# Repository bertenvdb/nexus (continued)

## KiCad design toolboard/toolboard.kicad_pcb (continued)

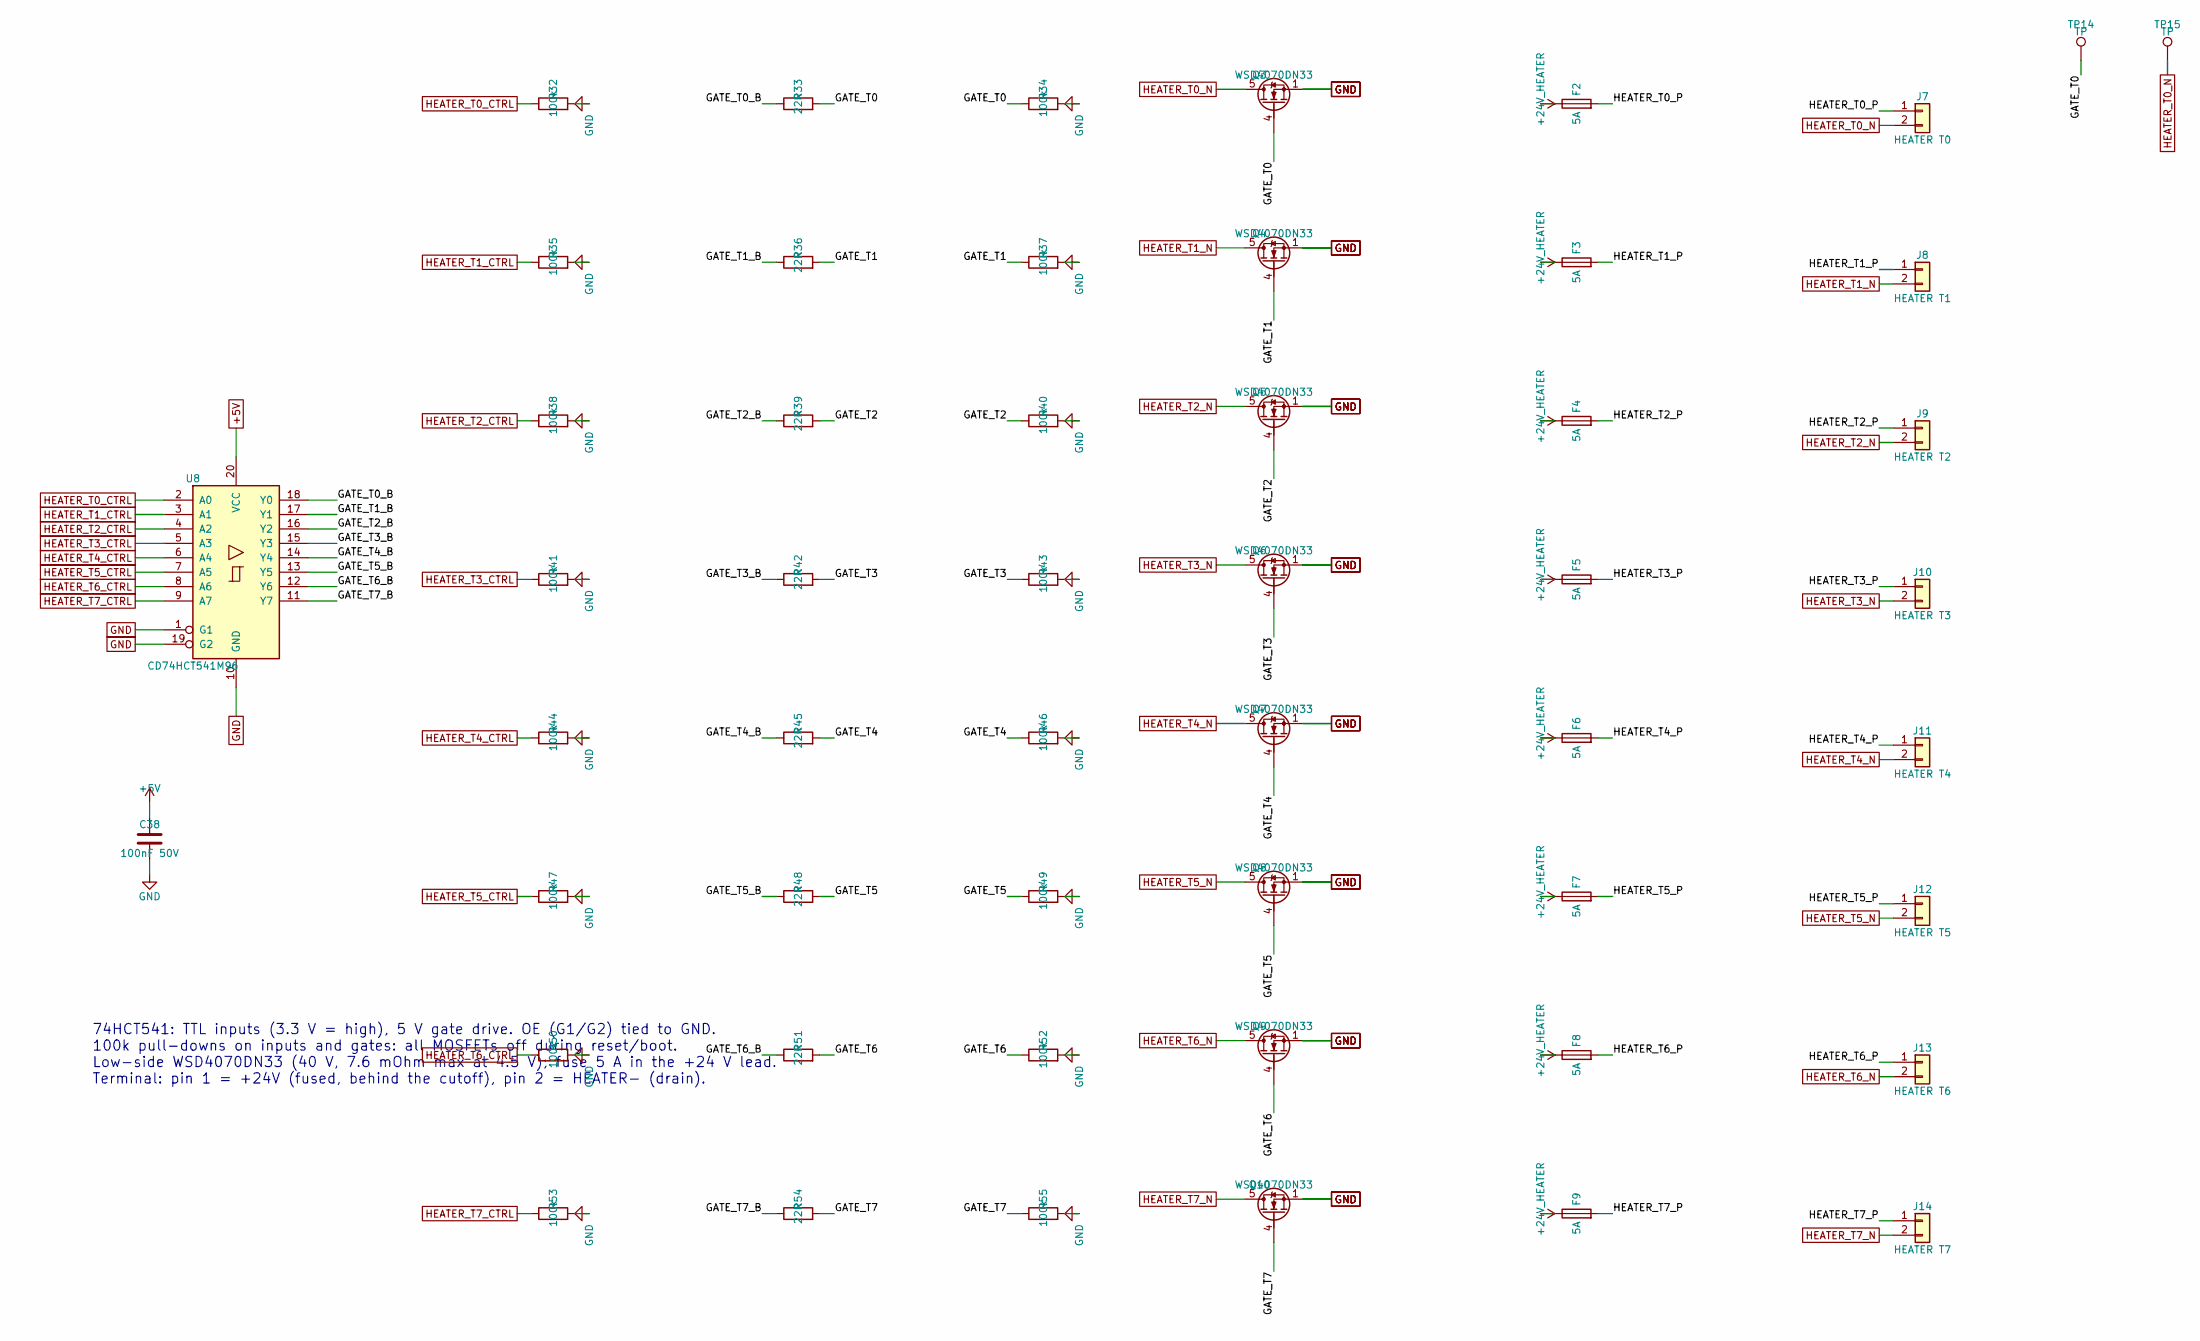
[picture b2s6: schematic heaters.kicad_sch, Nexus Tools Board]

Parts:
C38: 100nF 50V; C_0603_1608Metric; MPN CC0603KRX7R9BB104; LCSC C14663
F2, F3, F4, F5, F6, F7, F8, F9: 5A; Fuse_1206_3216Metric; MPN 0466005.NRHF; LCSC C57525
J7: HEATER T0; TerminalBlock_Phoenix_MKDS-1,5-2-5.08_1x02_P5.08mm_Horizont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; MPN WJ500V-5.08-2P; LCSC C8465
J8: HEATER T1; TerminalBlock_Phoenix_MKDS-1,5-2-5.08_1x02_P5.08mm_Horizont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; MPN WJ500V-5.08-2P; LCSC C8465
J9: HEATER T2; TerminalBlock_Phoenix_MKDS-1,5-2-5.08_1x02_P5.08mm_Horizont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; MPN WJ500V-5.08-2P; LCSC C8465
J10: HEATER T3; TerminalBlock_Phoenix_MKDS-1,5-2-5.08_1x02_P5.08mm_Horizont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; MPN WJ500V-5.08-2P; LCSC C8465
J11: HEATER T4; TerminalBlock_Phoenix_MKDS-1,5-2-5.08_1x02_P5.08mm_Horizont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; MPN WJ500V-5.08-2P; LCSC C8465
J12: HEATER T5; TerminalBlock_Phoenix_MKDS-1,5-2-5.08_1x02_P5.08mm_Horizont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; MPN WJ500V-5.08-2P; LCSC C8465
J13: HEATER T6; TerminalBlock_Phoenix_MKDS-1,5-2-5.08_1x02_P5.08mm_Horizont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; MPN WJ500V-5.08-2P; LCSC C8465
J14: HEATER T7; TerminalBlock_Phoenix_MKDS-1,5-2-5.08_1x02_P5.08mm_Horizont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; MPN WJ500V-5.08-2P; LCSC C8465
Q3, Q4, Q5, Q6, Q7, Q8, Q9, Q10: WSD4070DN33; PDFN3333-8_L3.1-W3.2-P0.65-LS3.4-BL; MPN WSD4070DN33; LCSC C719095
R32, R34, R35, R37, R38, R40, R41, R43, R44, R46, R47, R49, R50, R52, R53, R55: 100k; R_0603_1608Metric; MPN 0603WAF1003T5E; LCSC C25803
R33, R36, R39, R42, R45, R48, R51, R54: 22R; R_0603_1608Metric; MPN 0603WAF220JT5E; LCSC C23345
TP14, TP15: TP; TestPoint_Pad_D1.5mm
U8: CD74HCT541M96; SOIC-20W_7.5x12.8mm_P1.27mm; MPN CD74HCT541M96; LCSC C6560

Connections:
+5V: C38.1, U8.20 (VCC); also elsewhere on the board
+24V_HEATER: F2.1, F3.1, F4.1, F5.1, F6.1, F7.1, F8.1, F9.1; also elsewhere on the board
/heaters/GATE_T0: Q3.4 (G), R33.2, R34.1, TP14.1
/heaters/GATE_T0_B: R33.1, U8.18 (Y0)
/heaters/GATE_T1: Q4.4 (G), R36.2, R37.1
/heaters/GATE_T1_B: R36.1, U8.17 (Y1)
/heaters/GATE_T2: Q5.4 (G), R39.2, R40.1
/heaters/GATE_T2_B: R39.1, U8.16 (Y2)
/heaters/GATE_T3: Q6.4 (G), R42.2, R43.1
/heaters/GATE_T3_B: R42.1, U8.15 (Y3)
/heaters/GATE_T4: Q7.4 (G), R45.2, R46.1
/heaters/GATE_T4_B: R45.1, U8.14 (Y4)
/heaters/GATE_T5: Q8.4 (G), R48.2, R49.1
/heaters/GATE_T5_B: R48.1, U8.13 (Y5)
/heaters/GATE_T6: Q9.4 (G), R51.2, R52.1
/heaters/GATE_T6_B: R51.1, U8.12 (Y6)
/heaters/GATE_T7: Q10.4 (G), R54.2, R55.1
/heaters/GATE_T7_B: R54.1, U8.11 (Y7)
/heaters/HEATER_T0_P: F2.2, J7.1
/heaters/HEATER_T1_P: F3.2, J8.1
/heaters/HEATER_T2_P: F4.2, J9.1
/heaters/HEATER_T3_P: F5.2, J10.1
/heaters/HEATER_T4_P: F6.2, J11.1
/heaters/HEATER_T5_P: F7.2, J12.1
/heaters/HEATER_T6_P: F8.2, J13.1
/heaters/HEATER_T7_P: F9.2, J14.1
GND: C38.2, Q3.1 (S), Q3.2 (S), Q3.3 (S), Q4.1 (S), Q4.2 (S), Q4.3 (S), Q5.1 (S), Q5.2 (S), Q5.3 (S), Q6.1 (S), Q6.2 (S), Q6.3 (S), Q7.1 (S), Q7.2 (S), Q7.3 (S), Q8.1 (S), Q8.2 (S), Q8.3 (S), Q9.1 (S), Q9.2 (S), Q9.3 (S), Q10.1 (S), Q10.2 (S), Q10.3 (S), R32.2, R34.2, R35.2, R37.2, R38.2, R40.2, R41.2, R43.2, R44.2, R46.2, R47.2, R49.2, R50.2, R52.2, R53.2, R55.2, U8.1 (G1), U8.10 (GND), U8.19 (G2); also elsewhere on the board
HEATER_T0_CTRL: R32.1, U8.2 (A0); also elsewhere on the board
HEATER_T0_N: J7.2, Q3.5 (D), TP15.1; also elsewhere on the board
HEATER_T1_CTRL: R35.1, U8.3 (A1); also elsewhere on the board
HEATER_T1_N: J8.2, Q4.5 (D); also elsewhere on the board
HEATER_T2_CTRL: R38.1, U8.4 (A2); also elsewhere on the board
HEATER_T2_N: J9.2, Q5.5 (D); also elsewhere on the board
HEATER_T3_CTRL: R41.1, U8.5 (A3); also elsewhere on the board
HEATER_T3_N: J10.2, Q6.5 (D); also elsewhere on the board
HEATER_T4_CTRL: R44.1, U8.6 (A4); also elsewhere on the board
HEATER_T4_N: J11.2, Q7.5 (D); also elsewhere on the board
HEATER_T5_CTRL: R47.1, U8.7 (A5); also elsewhere on the board
HEATER_T5_N: J12.2, Q8.5 (D); also elsewhere on the board
HEATER_T6_CTRL: R50.1, U8.8 (A6); also elsewhere on the board
HEATER_T6_N: J13.2, Q9.5 (D); also elsewhere on the board
HEATER_T7_CTRL: R53.1, U8.9 (A7); also elsewhere on the board
HEATER_T7_N: J14.2, Q10.5 (D); also elsewhere on the board

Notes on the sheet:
74HCT541: TTL inputs (3.3 V = high), 5 V gate drive. OE (G1/G2) tied to GND. 100k pull-downs on inputs and gates: all MOSFETs off during reset/boot. Low-side WSD4070DN33 (40 V, 7.6 mOhm max at 4.5 V); fuse 5 A in the +24 V lead. Terminal: pin 1 = +24V (fused, behind the cutoff), pin 2 = HEATER- (dr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

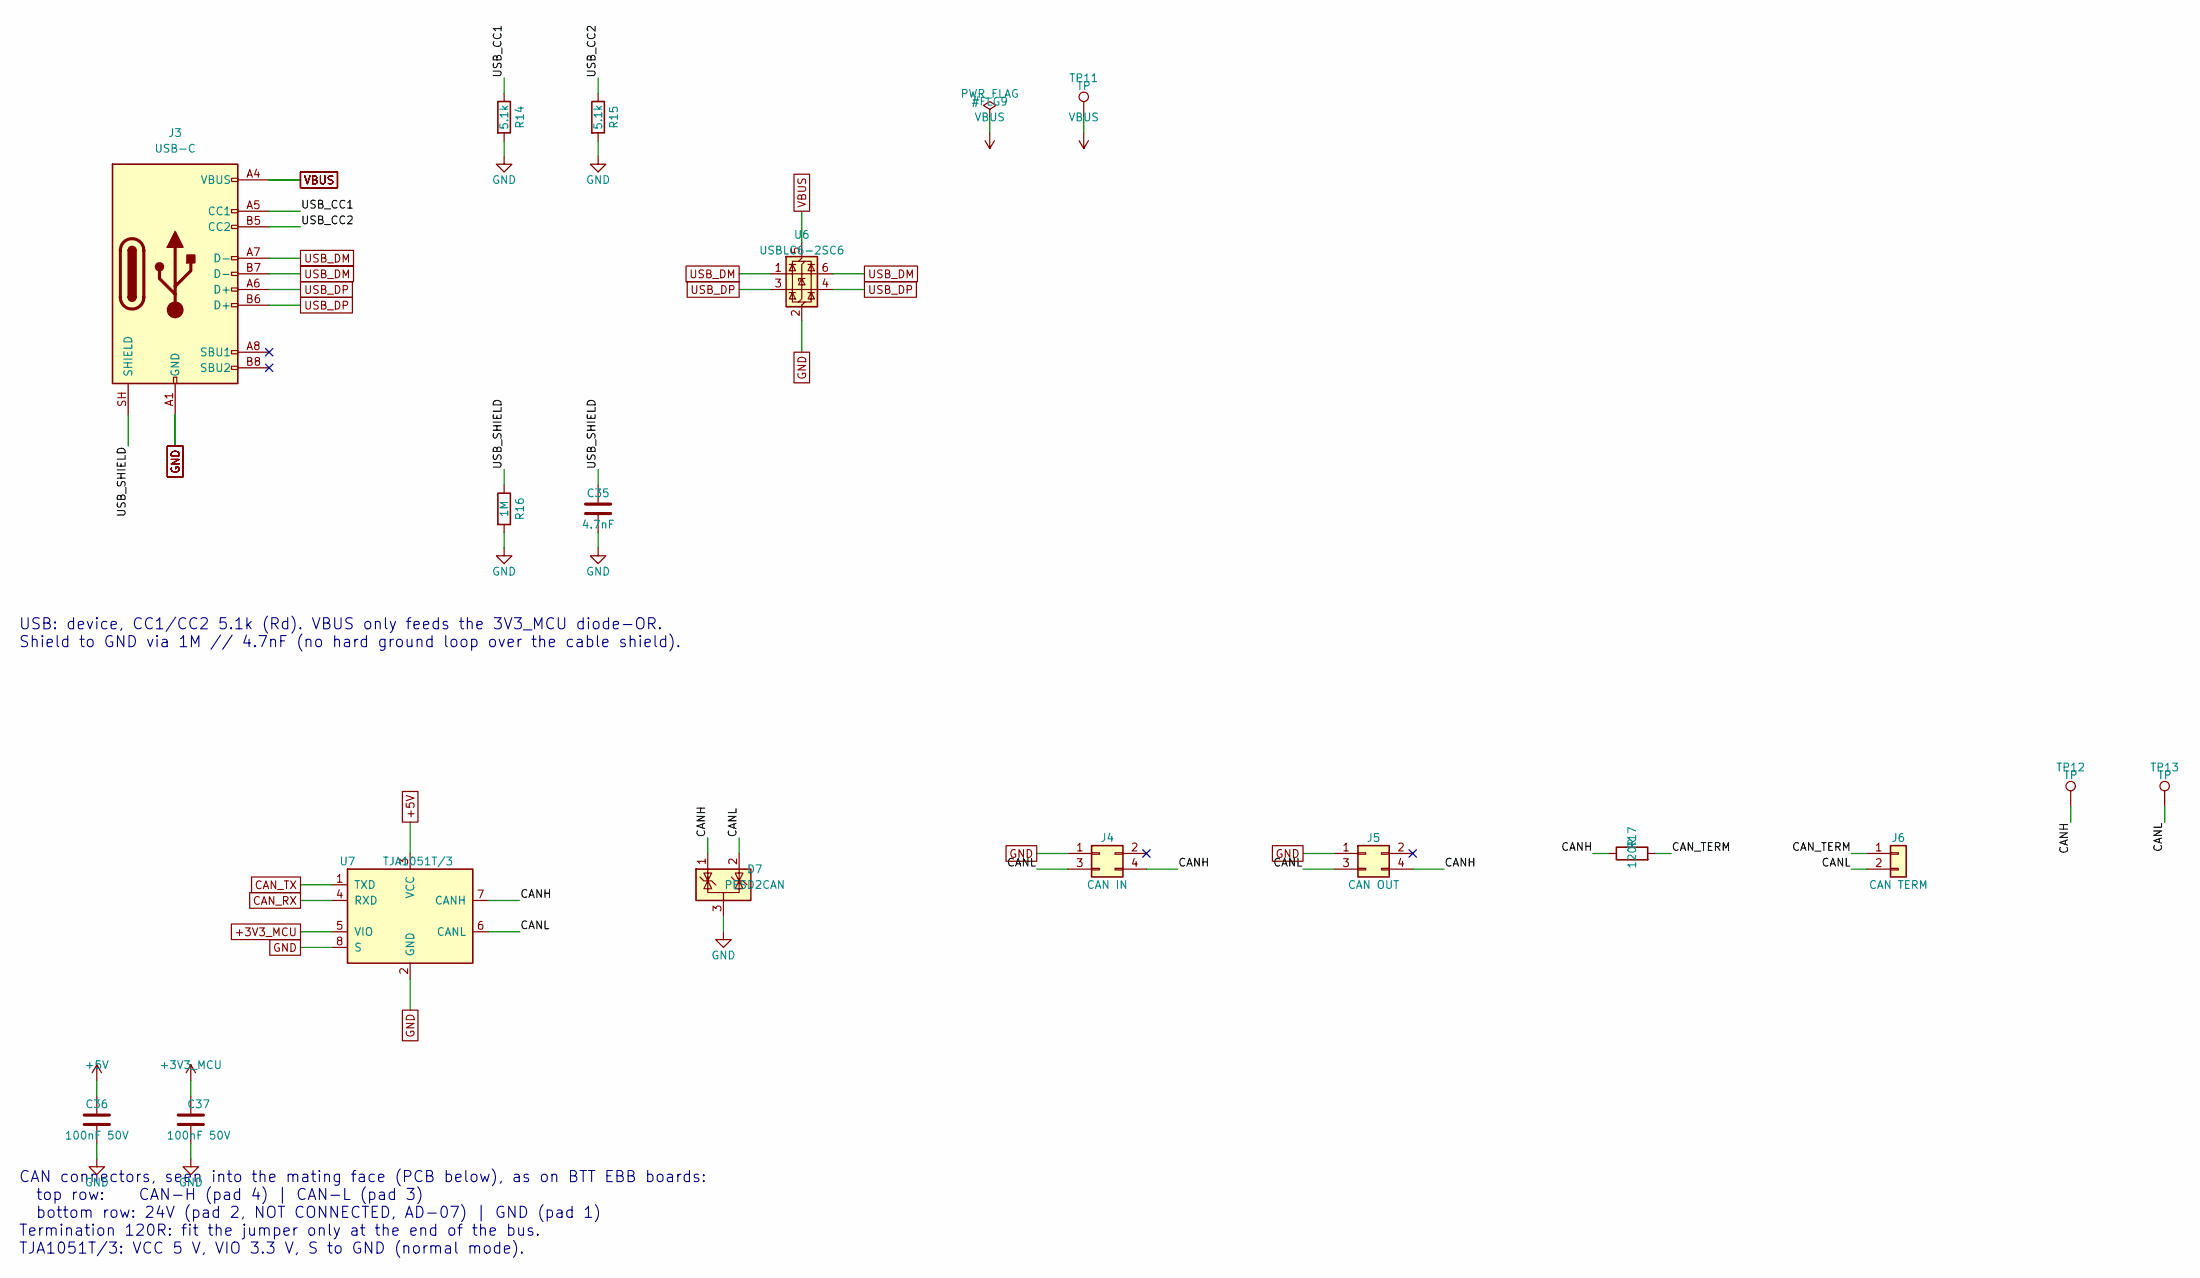
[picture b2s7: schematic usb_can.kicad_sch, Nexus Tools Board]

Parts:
C35: 4.7nF; C_0603_1608Metric; MPN 0603B472K500NT; LCSC C53987
C36, C37: 100nF 50V; C_0603_1608Metric; MPN CC0603KRX7R9BB104; LCSC C14663
D7: PESD2CAN; SOT-23; MPN PESD2CAN; LCSC C907830
J3: USB-C; USB_C_Receptacle_HRO_TYPE-C-31-M-12; MPN TYPE-C-31-M-12; LCSC C165948
J4: CAN IN; Molex_Micro-Fit_3.0_43045-0400_2x02_P3.00mm_Horizontal; MPN 43045-0400; LCSC C122413
J5: CAN OUT; Molex_Micro-Fit_3.0_43045-0400_2x02_P3.00mm_Horizontal; MPN 43045-0400; LCSC C122413
J6: CAN TERM; PinHeader_1x02_P2.54mm_Vertical; MPN PZ254V-11-02P; LCSC C492401
R14, R15: 5.1k; R_0603_1608Metric; MPN 0603WAF5101T5E; LCSC C23186
R16: 1M; R_0603_1608Metric; MPN 0603WAF1004T5E; LCSC C22935
R17: 120R; R_0603_1608Metric; MPN 0603WAF1200T5E; LCSC C22787
TP11, TP12, TP13: TP; TestPoint_Pad_D1.5mm
U6: USBLC6-2SC6; SOT-23-6; MPN USBLC6-2SC6; LCSC C7519
U7: TJA1051T/3; SOIC-8_3.9x4.9mm_P1.27mm; MPN TJA1051T/3/1J; LCSC C38695

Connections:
+3V3_MCU: C37.1, U7.5 (VIO); also elsewhere on the board
+5V: C36.1, U7.3 (VCC); also elsewhere on the board
/usb_can/CANH: D7.1 (K), J4.4, J5.4, R17.1, TP12.1, U7.7 (CANH)
/usb_can/CANL: D7.2 (K), J4.3, J5.3, J6.2, TP13.1, U7.6 (CANL)
/usb_can/CAN_TERM: J6.1, R17.2
/usb_can/USB_CC1: J3.A5 (CC1), R14.1
/usb_can/USB_CC2: J3.B5 (CC2), R15.1
/usb_can/USB_SHIELD: C35.1, J3.SH (SHIELD), R16.1
CAN_RX: U7.4 (RXD); also elsewhere on the board
CAN_TX: U7.1 (TXD); also elsewhere on the board
GND: C35.2, C36.2, C37.2, D7.3 (A), J3.A1 (GND), J3.A12 (GND), J3.B1 (GND), J3.B12 (GND), J4.1, J5.1, R14.2, R15.2, R16.2, U6.2 (GND), U7.2 (GND), U7.8 (S); also elsewhere on the board
USB_DM: J3.A7 (D-), J3.B7 (D-), U6.1 (I/O1), U6.6 (I/O1); also elsewhere on the board
USB_DP: J3.A6 (D+), J3.B6 (D+), U6.3 (I/O2), U6.4 (I/O2); also elsewhere on the board
VBUS: J3.A4 (VBUS), J3.A9 (VBUS), J3.B4 (VBUS), J3.B9 (VBUS), TP11.1, U6.5 (VBUS); also elsewhere on the board

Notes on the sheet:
CAN connectors, seen into the mating face (PCB below), as on BTT EBB boards: top row: CAN-H (pad 4) | CAN-L (pad 3) bottom row: 24V (pad 2, NOT CONNECTED, AD-07) | GND (pad 1) Termination 120R: fit the jumper only at the end of the bus. TJA1051T/3: VCC 5 V, VIO 3.3 V, S to GND (normal mode).
USB: device, CC1/CC2 5.1k (Rd). VBUS only feeds the 3V3_MCU diode-OR. Shield to GND via 1M // 4.7nF (no hard ground loop over the cable shield).

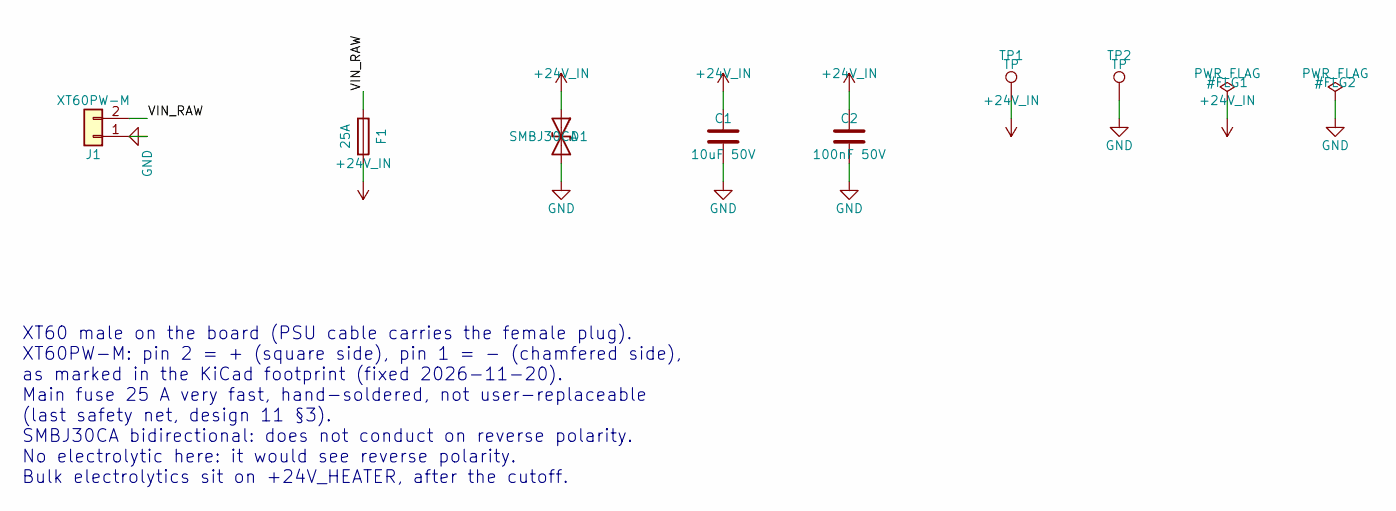
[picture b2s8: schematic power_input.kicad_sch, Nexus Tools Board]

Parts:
C1: 10uF 50V; C_1206_3216Metric; MPN CL31A106KBHNNNE; LCSC C13585
C2: 100nF 50V; C_0603_1608Metric; MPN CC0603KRX7R9BB104; LCSC C14663
D1: SMBJ30CA; D_SMB; MPN SMBJ30CA; LCSC C2925441
F1: 25A; FUSE-SMD_L10.1-W3.1; MPN 0456025.ER; LCSC C315877
J1: XT60PW-M; AMASS_XT60PW-M_1x02_P7.20mm_Horizontal; MPN XT60PW-M; LCSC C98732
TP1, TP2: TP; TestPoint_Pad_D1.5mm

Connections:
+24V_IN: C1.1, C2.1, D1.1 (A1), F1.2, TP1.1; also elsewhere on the board
/power_input/VIN_RAW: F1.1, J1.2
GND: C1.2, C2.2, D1.2 (A2), J1.1, TP2.1; also elsewhere on the board

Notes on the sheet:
XT60 male on the board (PSU cable carries the female plug). XT60PW-M: pin 2 = + (square side), pin 1 = - (chamfered side), as marked in the KiCad footprint (fixed 2026-11-20). Main fuse 25 A very fast, hand-soldered, not user-replaceable (last safety net, design 11 §3). SMBJ30CA bidirectional: does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

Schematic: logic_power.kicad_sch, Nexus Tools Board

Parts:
C12, C13: 10uF 50V; C_1206_3216Metric; MPN CL31A106KBHNNNE; LCSC C13585
C14, C17, C23, C27: 100nF 50V; C_0603_1608Metric; MPN CC0603KRX7R9BB104; LCSC C14663
C15: 22nF; C_0603_1608Metric; MPN CL10B223KB8NNNC; LCSC C21122
C16: 100pF C0G; C_0603_1608Metric; MPN CL10C101JB8NNNC; LCSC C14858
C18, C19, C20: 22uF 25V; C_1206_3216Metric; MPN CL31A226KAHNNNE; LCSC C12891
C21, C22, C24, C25, C26: 1uF 50V; C_0603_1608Metric; MPN CL10A105KB8NNNC; LCSC C15849
D3, D4: SS56C; D_SMC; MPN SS56C; LCSC C24138
D5, D6: B5819W; D_SOD-123; MPN B5819W SL; LCSC C8598
L1: 10uH; IND-SMD_L7.1-W6.6; MPN MWSA0603S-100MT; LCSC C132141
R6: 1M; R_0603_1608Metric; MPN 0603WAF1004T5E; LCSC C22935
R7: 68k; R_0603_1608Metric; MPN 0603WAF6802T5E; LCSC C23231
R8: 160k; R_0603_1608Metric; MPN 0603WAF1603T5E; LCSC C22813
R9, R11: 6.8k; R_0603_1608Metric; MPN 0603WAF6801T5E; LCSC C23212
R10: 36k; R_0603_1608Metric; MPN 0603WAF3602T5E; LCSC C23147
R12: 10R; R_0603_1608Metric; MPN 0603WAF100JT5E; LCSC C22859
TP6, TP7, TP8, TP9, TP10: TP; TestPoint_Pad_D1.5mm
U2: TPS54360B; TI_SO-PowerPAD-8_ThermalVias; MPN TPS54360BDDAR; LCSC C524806
U3, U4: ME6211C33; SOT-23-5; MPN ME6211C33M5G-N; LCSC C82942

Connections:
+3V3_AUX: C25.1, TP8.1, U4.5 (V_{OUT}); also elsewhere on the board
+3V3_MCU: C22.1, C23.1, R12.1, TP7.1, U3.5 (V_{OUT}); also elsewhere on the board
+5V: C18.1, C19.1, C20.1, C24.1, D5.2 (A), L1.2, R10.1, TP6.1, U4.1 (V_{IN}), U4.3 (CE); also elsewhere on the board
+24V_IN: D3.2 (A); also elsewhere on the board
/logic_power/+5V_OR: C21.1, D5.1 (K), D6.1 (K), U3.1 (V_{IN}), U3.3 (CE)
/logic_power/BUCK_BOOT: C17.1, U2.1 (BOOT)
/logic_power/BUCK_COMP: C16.1, R9.1, U2.6 (COMP)
/logic_power/BUCK_EN: R6.2, R7.1, U2.3 (EN)
/logic_power/BUCK_FB: R10.2, R11.1, U2.5 (FB)
/logic_power/BUCK_RT: R8.1, U2.4 (RT/CLK)
/logic_power/BUCK_SW: C17.2, D4.1 (K), L1.1, U2.8 (SW)
/logic_power/COMP_RC: C15.1, R9.2
/logic_power/VIN_BUCK: C12.1, C13.1, C14.1, D3.1 (K), R6.1, U2.2 (VIN)
AGND: C26.2, C27.2, TP10.1; also elsewhere on the board
GND: C12.2, C13.2, C14.2, C15.2, C16.2, C18.2, C19.2, C20.2, C21.2, C22.2, C23.2, C24.2, C25.2, D4.2 (A), R7.2, R8.2, R11.2, U2.7 (GND), U2.9 (GNDPAD), U3.2 (V_{SS}), U4.2 (V_{SS}); also elsewhere on the board
VBUS: D6.2 (A); also elsewhere on the board
VREF_A: C26.1, C27.1, R12.2, TP9.1; also elsewhere on the board

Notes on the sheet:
3V3_MCU: diode-OR of +5V and USB VBUS, so the MCU runs on USB alone (flashing without 24 V). VBUS feeds nothing else. 3V3_AUX: sensors, status LEDs. VREF_A = 3V3_MCU through 10R + 1uF + 100nF to AGND (ratiometric ADC).
TPS54360B, 604 kHz (RT 160k), Vout = 0.8 x (1 + 36k/6.8k) = 5.04 V. UVLO 1M/68k: start 17.6 V, stop 14.3 V. Compensation 6.8k + 22nF // 100pF. Catch diode SS56C: non-synchronous buck. Values: docs/calculations.md §1.

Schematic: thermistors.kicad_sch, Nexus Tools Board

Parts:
C39, C40, C41, C42, C43, C44, C45, C46, C47, C48, C49, C50, C51, C52, C53, C54: 100nF 50V; C_0603_1608Metric; MPN CC0603KRX7R9BB104; LCSC C14663
D22, D24, D26, D28, D30, D32, D34, D36: SMF30CA; D_SOD-123F; MPN SMF30CA; LCSC C19077519
D23, D25, D27, D29, D31, D33, D35, D37: BAT54S; SOT-23; MPN BAT54S; LCSC C408389
J15: THERM T0; JST_XH_B2B-XH-A_1x02_P2.50mm_Vertical; MPN B2B-XH-A(LF)(SN); LCSC C158012
J16: THERM T1; JST_XH_B2B-XH-A_1x02_P2.50mm_Vertical; MPN B2B-XH-A(LF)(SN); LCSC C158012
J17: THERM T2; JST_XH_B2B-XH-A_1x02_P2.50mm_Vertical; MPN B2B-XH-A(LF)(SN); LCSC C158012
J18: THERM T3; JST_XH_B2B-XH-A_1x02_P2.50mm_Vertical; MPN B2B-XH-A(LF)(SN); LCSC C158012
J19: THERM T4; JST_XH_B2B-XH-A_1x02_P2.50mm_Vertical; MPN B2B-XH-A(LF)(SN); LCSC C158012
J20: THERM T5; JST_XH_B2B-XH-A_1x02_P2.50mm_Vertical; MPN B2B-XH-A(LF)(SN); LCSC C158012
J21: THERM T6; JST_XH_B2B-XH-A_1x02_P2.50mm_Vertical; MPN B2B-XH-A(LF)(SN); LCSC C158012
J22: THERM T7; JST_XH_B2B-XH-A_1x02_P2.50mm_Vertical; MPN B2B-XH-A(LF)(SN); LCSC C158012
JP1, JP2, JP3, JP4, JP5, JP6, JP7, JP8: PT1000; SolderJumper-2_P1.3mm_Open_RoundedPad1.0x1.5mm
R56, R59, R62, R65, R68, R71, R74, R77: 4.7k 0.1%; R_0603_1608Metric; MPN TD03G4701BT; LCSC C666997
R57, R60, R63, R66, R69, R72, R75, R78: 4.12k 0.1%; R_0603_1608Metric; MPN AR03BTCX4121; LCSC C2984354
R58, R61, R64, R67, R70, R73, R76, R79: 4.7k; R_0603_1608Metric; MPN 0603WAF4701T5E; LCSC C23162

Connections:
/thermistors/THERM_T0_C: C39.1, D22.1 (A1), J15.1, R56.2, R57.2, R58.1
/thermistors/THERM_T0_PT: JP1.2 (B), R57.1
/thermistors/THERM_T1_C: C41.1, D24.1 (A1), J16.1, R59.2, R60.2, R61.1
/thermistors/THERM_T1_PT: JP2.2 (B), R60.1
/thermistors/THERM_T2_C: C43.1, D26.1 (A1), J17.1, R62.2, R63.2, R64.1
/thermistors/THERM_T2_PT: JP3.2 (B), R63.1
/thermistors/THERM_T3_C: C45.1, D28.1 (A1), J18.1, R65.2, R66.2, R67.1
/thermistors/THERM_T3_PT: JP4.2 (B), R66.1
/thermistors/THERM_T4_C: C47.1, D30.1 (A1), J19.1, R68.2, R69.2, R70.1
/thermistors/THERM_T4_PT: JP5.2 (B), R69.1
/thermistors/THERM_T5_C: C49.1, D32.1 (A1), J20.1, R71.2, R72.2, R73.1
/thermistors/THERM_T5_PT: JP6.2 (B), R72.1
/thermistors/THERM_T6_C: C51.1, D34.1 (A1), J21.1, R74.2, R75.2, R76.1
/thermistors/THERM_T6_PT: JP7.2 (B), R75.1
/thermistors/THERM_T7_C: C53.1, D36.1 (A1), J22.1, R77.2, R78.2, R79.1
/thermistors/THERM_T7_PT: JP8.2 (B), R78.1
AGND: C39.2, C40.2, C41.2, C42.2, C43.2, C44.2, C45.2, C46.2, C47.2, C48.2, C49.2, C50.2, C51.2, C52.2, C53.2, C54.2, D22.2 (A2), D23.1 (A), D24.2 (A2), D25.1 (A), D26.2 (A2), D27.1 (A), D28.2 (A2), D29.1 (A), D30.2 (A2), D31.1 (A), D32.2 (A2), D33.1 (A), D34.2 (A2), D35.1 (A), D36.2 (A2), D37.1 (A), J15.2, J16.2, J17.2, J18.2, J19.2, J20.2, J21.2, J22.2; also elsewhere on the board
THERM_T0: C40.1, D23.3 (COM), R58.2; also elsewhere on the board
THERM_T1: C42.1, D25.3 (COM), R61.2; also elsewhere on the board
THERM_T2: C44.1, D27.3 (COM), R64.2; also elsewhere on the board
THERM_T3: C46.1, D29.3 (COM), R67.2; also elsewhere on the board
THERM_T4: C48.1, D31.3 (COM), R70.2; also elsewhere on the board
THERM_T5: C50.1, D33.3 (COM), R73.2; also elsewhere on the board
THERM_T6: C52.1, D35.3 (COM), R76.2; also elsewhere on the board
THERM_T7: C54.1, D37.3 (COM), R79.2; also elsewhere on the board
VREF_A: D23.2 (K), D25.2 (K), D27.2 (K), D29.2 (K), D31.2 (K), D33.2 (K), D35.2 (K), D37.2 (K), JP1.1 (A), JP2.1 (A), JP3.1 (A), JP4.1 (A), JP5.1 (A), JP6.1 (A), JP7.1 (A), JP8.1 (A), R56.1, R59.1, R62.1, R65.1, R68.1, R71.1, R74.1, R77.1; also elsewhere on the board

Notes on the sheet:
Pull-up 4.7k 0.1 % (NTC 100K, pullup_resistor: 4700). Close JP = PT1000: 4.7k // 4.12k = 2195 Ohm (pullup_resistor: 2195). Pull-ups on VREF_A = ADC reference. 24 V on the input (heater wire touching the thermistor wire): 4.7k + BAT54S limit the ADC pin current to ~4 mA; SMF30CA does not conduct at 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

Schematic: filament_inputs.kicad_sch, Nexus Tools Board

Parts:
C55: 10uF 50V; C_1206_3216Metric; MPN CL31A106KBHNNNE; LCSC C13585
C56, C57, C58, C59, C60, C61, C62, C63, C64, C65, C66, C67, C68, C69, C70, C71: 100nF 50V; C_0603_1608Metric; MPN CC0603KRX7R9BB104; LCSC C14663
D38, D39, D40, D41, D42, D43, D44, D45, D46, D47, D48, D49, D50, D51, D52, D53, D54: PESD5V0S1BA; D_SOD-323; MPN PESD5V0S1BA; LCSC C2827694
F10: 0.75A; Fuse_1206_3216Metric; MPN JK-nSMD075-16; LCSC C409806
J23: FIL T0; JST_XH_B4B-XH-A_1x04_P2.50mm_Vertical; MPN B4B-XH-A(LF)(SN); LCSC C144395
J24: FIL T1; JST_XH_B4B-XH-A_1x04_P2.50mm_Vertical; MPN B4B-XH-A(LF)(SN); LCSC C144395
J25: FIL T2; JST_XH_B4B-XH-A_1x04_P2.50mm_Vertical; MPN B4B-XH-A(LF)(SN); LCSC C144395
J26: FIL T3; JST_XH_B4B-XH-A_1x04_P2.50mm_Vertical; MPN B4B-XH-A(LF)(SN); LCSC C144395
J27: FIL T4; JST_XH_B4B-XH-A_1x04_P2.50mm_Vertical; MPN B4B-XH-A(LF)(SN); LCSC C144395
J28: FIL T5; JST_XH_B4B-XH-A_1x04_P2.50mm_Vertical; MPN B4B-XH-A(LF)(SN); LCSC C144395
J29: FIL T6; JST_XH_B4B-XH-A_1x04_P2.50mm_Vertical; MPN B4B-XH-A(LF)(SN); LCSC C144395
J30: FIL T7; JST_XH_B4B-XH-A_1x04_P2.50mm_Vertical; MPN B4B-XH-A(LF)(SN); LCSC C144395
JP9: VCC_FIL 5V|3V3; SolderJumper-3_P1.3mm_Bridged12_RoundedPad1.0x1.5mm
R80, R82, R84, R86, R88, R90, R92, R94, R96, R98, R100, R102, R104, R106, R108, R110: 1k; R_0603_1608Metric; MPN 0603WAF1001T5E; LCSC C21190
R81, R83, R85, R87, R89, R91, R93, R95, R97, R99, R101, R103, R105, R107, R109, R111: 10k; R_0603_1608Metric; MPN 0603WAF1002T5E; LCSC C25804

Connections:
+3V3_AUX: JP9.3 (B); also elsewhere on the board
+3V3_MCU: R81.1, R83.1, R85.1, R87.1, R89.1, R91.1, R93.1, R95.1, R97.1, R99.1, R101.1, R103.1, R105.1, R107.1, R109.1, R111.1; also elsewhere on the board
+5V: JP9.1 (A); also elsewhere on the board
/filament_inputs/FIL_MOTION_T0_C: D40.1 (A1), J23.4, R82.1
/filament_inputs/FIL_MOTION_T1_C: D42.1 (A1), J24.4, R86.1
/filament_inputs/FIL_MOTION_T2_C: D44.1 (A1), J25.4, R90.1
/filament_inputs/FIL_MOTION_T3_C: D46.1 (A1), J26.4, R94.1
/filament_inputs/FIL_MOTION_T4_C: D48.1 (A1), J27.4, R98.1
/filament_inputs/FIL_MOTION_T5_C: D50.1 (A1), J28.4, R102.1
/filament_inputs/FIL_MOTION_T6_C: D52.1 (A1), J29.4, R106.1
/filament_inputs/FIL_MOTION_T7_C: D54.1 (A1), J30.4, R110.1
/filament_inputs/FIL_RUNOUT_T0_C: D39.1 (A1), J23.1, R80.1
/filament_inputs/FIL_RUNOUT_T1_C: D41.1 (A1), J24.1, R84.1
/filament_inputs/FIL_RUNOUT_T2_C: D43.1 (A1), J25.1, R88.1
/filament_inputs/FIL_RUNOUT_T3_C: D45.1 (A1), J26.1, R92.1
/filament_inputs/FIL_RUNOUT_T4_C: D47.1 (A1), J27.1, R96.1
/filament_inputs/FIL_RUNOUT_T5_C: D49.1 (A1), J28.1, R100.1
/filament_inputs/FIL_RUNOUT_T6_C: D51.1 (A1), J29.1, R104.1
/filament_inputs/FIL_RUNOUT_T7_C: D53.1 (A1), J30.1, R108.1
/filament_inputs/VCC_FIL: C55.1, D38.1 (A1), F10.2, J23.3, J24.3, J25.3, J26.3, J27.3, J28.3, J29.3, J30.3
/filament_inputs/VCC_FIL_SEL: F10.1, JP9.2 (C)
FIL_MOTION_T0: C57.1, R82.2, R83.2; also elsewhere on the board
FIL_MOTION_T1: C59.1, R86.2, R87.2; also elsewhere on the board
FIL_MOTION_T2: C61.1, R90.2, R91.2; also elsewhere on the board
FIL_MOTION_T3: C63.1, R94.2, R95.2; also elsewhere on the board
FIL_MOTION_T4: C65.1, R98.2, R99.2; also elsewhere on the board
FIL_MOTION_T5: C67.1, R102.2, R103.2; also elsewhere on the board
FIL_MOTION_T6: C69.1, R106.2, R107.2; also elsewhere on the board
FIL_MOTION_T7: C71.1, R110.2, R111.2; also elsewhere on the board
FIL_RUNOUT_T0: C56.1, R80.2, R81.2; also elsewhere on the board
FIL_RUNOUT_T1: C58.1, R84.2, R85.2; also elsewhere on the board
FIL_RUNOUT_T2: C60.1, R88.2, R89.2; also elsewhere on the board
FIL_RUNOUT_T3: C62.1, R92.2, R93.2; also elsewhere on the board
FIL_RUNOUT_T4: C64.1, R96.2, R97.2; also elsewhere on the board
FIL_RUNOUT_T5: C66.1, R100.2, R101.2; also elsewhere on the board
FIL_RUNOUT_T6: C68.1, R104.2, R105.2; also elsewhere on the board
FIL_RUNOUT_T7: C70.1, R108.2, R109.2; also elsewhere on the board
GND: C55.2, C56.2, C57.2, C58.2, C59.2, C60.2, C61.2, C62.2, C63.2, C64.2, C65.2, C66.2, C67.2, C68.2, C69.2, C70.2, C71.2, D38.2 (A2), D39.2 (A2), D40.2 (A2), D41.2 (A2), D42.2 (A2), D43.2 (A2), D44.2 (A2), D45.2 (A2), D46.2 (A2), D47.2 (A2), D48.2 (A2), D49.2 (A2), D50.2 (A2), D51.2 (A2), D52.2 (A2), D53.2 (A2), D54.2 (A2), J23.2, J24.2, J25.2, J26.2, J27.2, J28.2, J29.2, J30.2; also elsewhere on the board

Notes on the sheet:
Port: 1 RUNOUT, 2 GND, 3 VCC, 4 MOTION (silkscreen). D2F: pins 1 + 2. Inputs: 1k + 100nF (tau 0.1 ms), 10k pull-up to 3V3 (unplugged = high), FT pins (5V tolerant). VCC_FIL default 5 V (jumper 1-2); 3.3 V via 2-3: max 100 mA total.

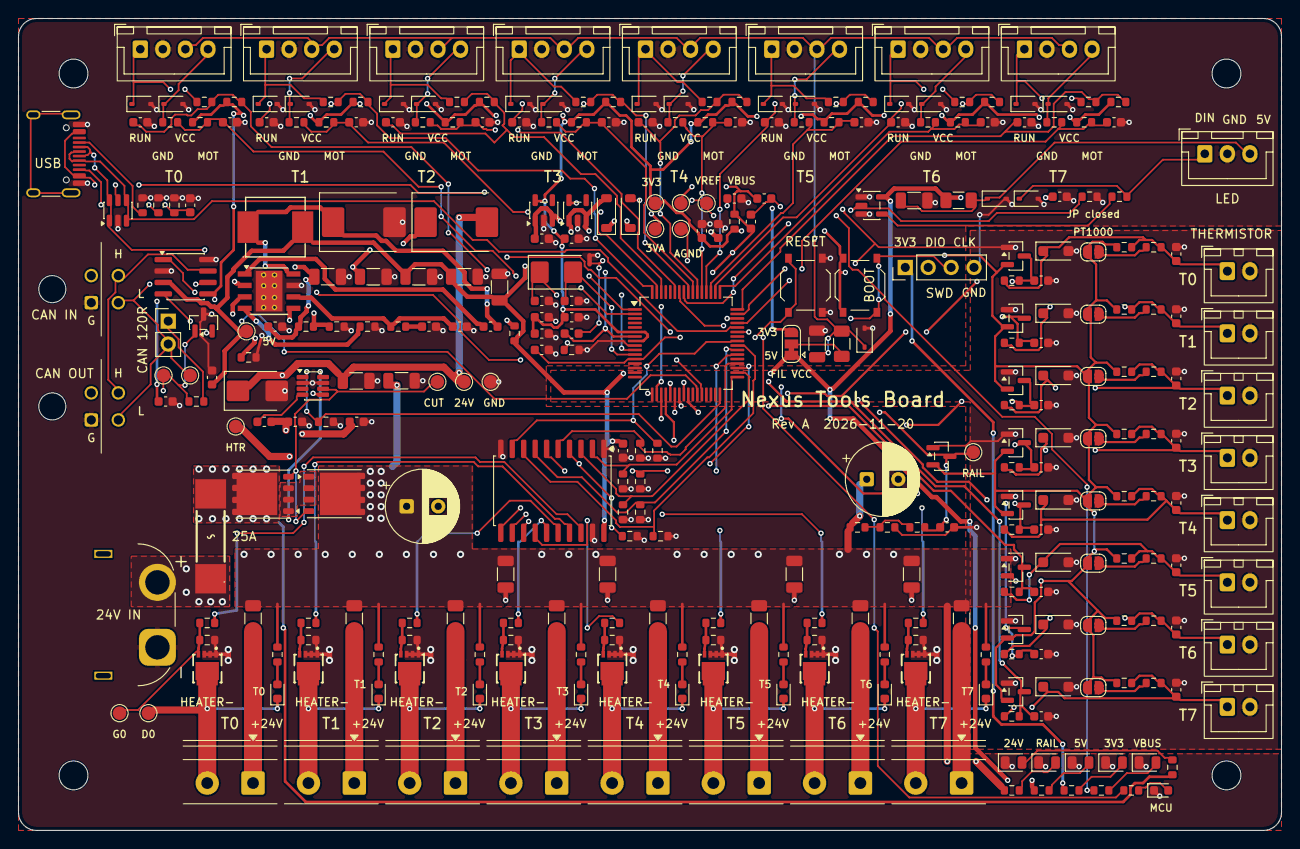
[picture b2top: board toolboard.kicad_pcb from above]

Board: 4 copper layers, 140.0 x 90.0 mm, 336 parts (0 on the bottom side), 157 nets.

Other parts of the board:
H1, H2, H3, H4: M3; MountingHole_3.2mm_M3

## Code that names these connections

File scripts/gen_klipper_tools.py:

#!/usr/bin/env python3
# SPDX-License-Identifier: GPL-3.0-or-later
"""Generate the per-tool Klipper files in klipper/nexus/tools and
klipper/nexus/filament from the board pinouts.

Pins: docs/pinout-toolboard.md and docs/pinout-dockboard.md.
Run after a pinout change:  python3 scripts/gen_klipper_tools.py
"""
from pathlib import Path

ROOT = Path(__file__).resolve().parent.parent / "klipper" / "nexus"

# tool: (heater, thermistor, runout, motion, dock fan, spare pin for the
# disabled placeholder heater)
PINS = {
    0: ("PB13", "PA0", "PC12", "PC11", "PB13", "PC0"),
    1: ("PB14", "PA1", "PC10", "PB9", "PB14", "PC1"),
    2: ("PB15", "PA2", "PB8", "PB5", "PB15", "PC2"),
    3: ("PA8", "PA3", "PD6", "PD5", "PA8", "PC3"),
    4: ("PC6", "PA4", "PD4", "PD3", "PC6", "PC5"),
    5: ("PC7", "PA5", "PD2", "PD1", "PC7", "PB2"),
    6: ("PD8", "PA6", "PD0", "PC9", "PD8", "PB10"),
    7: ("PD9", "PA7", "PC8", "PA15", "PD9", "PB11"),
}

HEADER = "# SPDX-License-Identifier: GPL-3.0-or-later\n# Generated by scripts/gen_klipper_tools.py. Do not edit.\n"

TOOL_VARS = """[gcode_macro _NEXUS_T{t}]
variable_enabled: {enabled}
variable_dock_x: 0.0
variable_dock_y: 0.0
variable_offset_x: 0.0
variable_offset_y: 0.0
variable_offset_z: 0.0
gcode:
"""


def ext(t):
    return "extruder" if t == 0 else f"extruder{t}"


def tool(t, p):
    heater, therm, _, _, fan, _ = p
    return (HEADER
            + f"# Nexus tool T{t}: pins and defaults. Override settings in nexus.cfg.\n\n"
            + TOOL_VARS.format(t=t, enabled="True")
            + f"""
[{ext(t)}]
heater_pin: nexus_tools:{heater}
sensor_pin: nexus_tools:{therm}
sensor_type: Generic 3950
# 4700 = PT1000 jumper open (NTC), 2195 = jumper closed (PT1000)
pullup_resistor: 4700
nozzle_diameter: 0.400
filament_diameter: 1.750
# The YUDX latch moves E together with X/Y; allow that.
max_extrude_cross_section: 5.0
max_extrude_only_distance: 101.0
min_temp: 0
max_temp: 300
min_extrude_temp: 170

[heater_fan nexus_dock_fan_t{t}]
pin: nexus_docks:{fan}
heater: {ext(t)}
heater_temp: 50.0

[gcode_macro T{t}]
description: Select tool {t}
gcode:
  NEXUS_CHANGE_TOOL TOOL={t}
""")


def disabled(t, p):
    spare = p[5]
    return (HEADER
            + f"""# Nexus tool T{t}: DISABLED placeholder.
# Klipper loads extruder, extruder1, ... up to the first missing number, so a
# disabled tool in the middle needs a placeholder to keep the higher tools.
# The heater drives an unused MCU pin and the "thermistor" is the MCU
# temperature. The macros refuse to heat or select this tool.

"""
            + TOOL_VARS.format(t=t, enabled="False")
            + f"""
[{ext(t)}]
heater_pin: nexus_tools:{spare}
sensor_type: temperature_combined
sensor_list: temperature_sensor nexus_tools_mcu
combination_method: max
maximum_deviation: 500
min_temp: -40
max_temp: 150
min_extrude_temp: 150
nozzle_diameter: 0.400
filament_diameter: 1.750
control: watermark

[gcode_macro T{t}]
description: Tool {t} is disabled
gcode:
  {{action_raise_error("Nexus: T{t} is disabled in nexus.cfg")}}
""")


def runout(t, p):
    return (HEADER
            + f"""# Nexus tool T{t}: runout switch on filament connector pin 1.
# Default: D2F with COM to GND (pin 2) and NO to pin 1, low = filament.
# For a sensor with the opposite logic, override switch_pin in nexus.cfg
# without the '!': switch_pin: nexus_tools:{p[2]}

[filament_switch_sensor nexus_t{t}_runout]
switch_pin: !nexus_tools:{p[2]}
pause_on_runout: False
runout_gcode: _NEXUS_RUNOUT TOOL={t} SENSOR=runout
insert_gcode: _NEXUS_INSERT TOOL={t}
""")


def motion(t, p):
    return (HEADER
            + f"""# Nexus tool T{t}: filament motion (clog) sensor on filament connector pin 4.
# Bound to the shared extruder drive; only enabled while T{t} is mounted.

[filament_motion_sensor nexus_t{t}_motion]
switch_pin: nexus_tools:{p[3]}
detection_length: 10.0
extruder: extruder_stepper nexus_extruder
pause_on_runout: False
runout_gcode: _NEXUS_RUNOUT TOOL={t} SENSOR=motion
""")


def main():
    for t, p in PINS.items():
        (ROOT / "tools" / f"t{t}.cfg").write_text(tool(t, p))
        (ROOT / "tools" / f"t{t}_disabled.cfg").write_text(disabled(t, p))
        (ROOT / "filament" / f"t{t}_runout.cfg").write_text(runout(t, p))
        (ROOT / "filament" / f"t{t}_motion.cfg").write_text(motion(t, p))


if __name__ == "__main__":
    main()

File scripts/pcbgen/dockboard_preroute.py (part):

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  +24V_IN    fuse -> RPP FET source pins, TVS, LM74502 sense pins: F.Cu
             polygon; the FET gate pin it surrounds escapes through a via
  +24V_INT   RPP FET drain -> bulk capacitor, 6 vias 0.8/0.4 to the In2 plane
  BUCK_SW    5 V buck: SW pin -> catch diode -> inductor -> BOOT capacitor
  FBK_SW     fan buck: the same
  FAN_BUCK   fan buck inductor -> 3 vias 0.8/0.4 to the B.Cu FAN_BUCK plane
  USB        USB-C pin pairs joined (DM left, DP right of the pads), to U_USBESD
  JP_FRAIL   pin 1 (+24V_INT) via 0.8/0.4 to In2; pin 2 (FAN_RAIL) 1.0 mm
             track between the pads of C_FOUT to 2 vias 0.8/0.4 to the In2
             FAN_RAIL plane; pin 3 (FAN_BUCK) via 0.8/0.4 to the B.Cu plane
  catch diodes  anode pads of D_CATCH / D_FCATCH: GND polygon + 3 vias 0.8/0.4

Coordinates are board mm for the placement of dockboard_place.py
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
